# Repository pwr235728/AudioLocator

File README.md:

# AudioLocator
Urządzenie umożliwiające wykrycie kierunku nadchodzącego dźwięku o znanych parametrach (sinusoidalny, o znanej częstotliwość).

Urządzenie składa się z:
* dwóch mikrofonów
* dwóch wzmacniaczy mikrofonowych 
* mikrokontroler STM32.

Mikrokontroler na podstawie dźwięku przechwyconego mikrofonami, oblicza kierunek z którego nadchodzi dźwięk.

Docelowo urządzenie ma zostać wyposarzone w dodatkowe mikrofony i umożłiwiać wykrywanie pozycji 3D źródła dźwięku.

## Model pytki PCB ze wzmacniaczami mikrofonowymi:

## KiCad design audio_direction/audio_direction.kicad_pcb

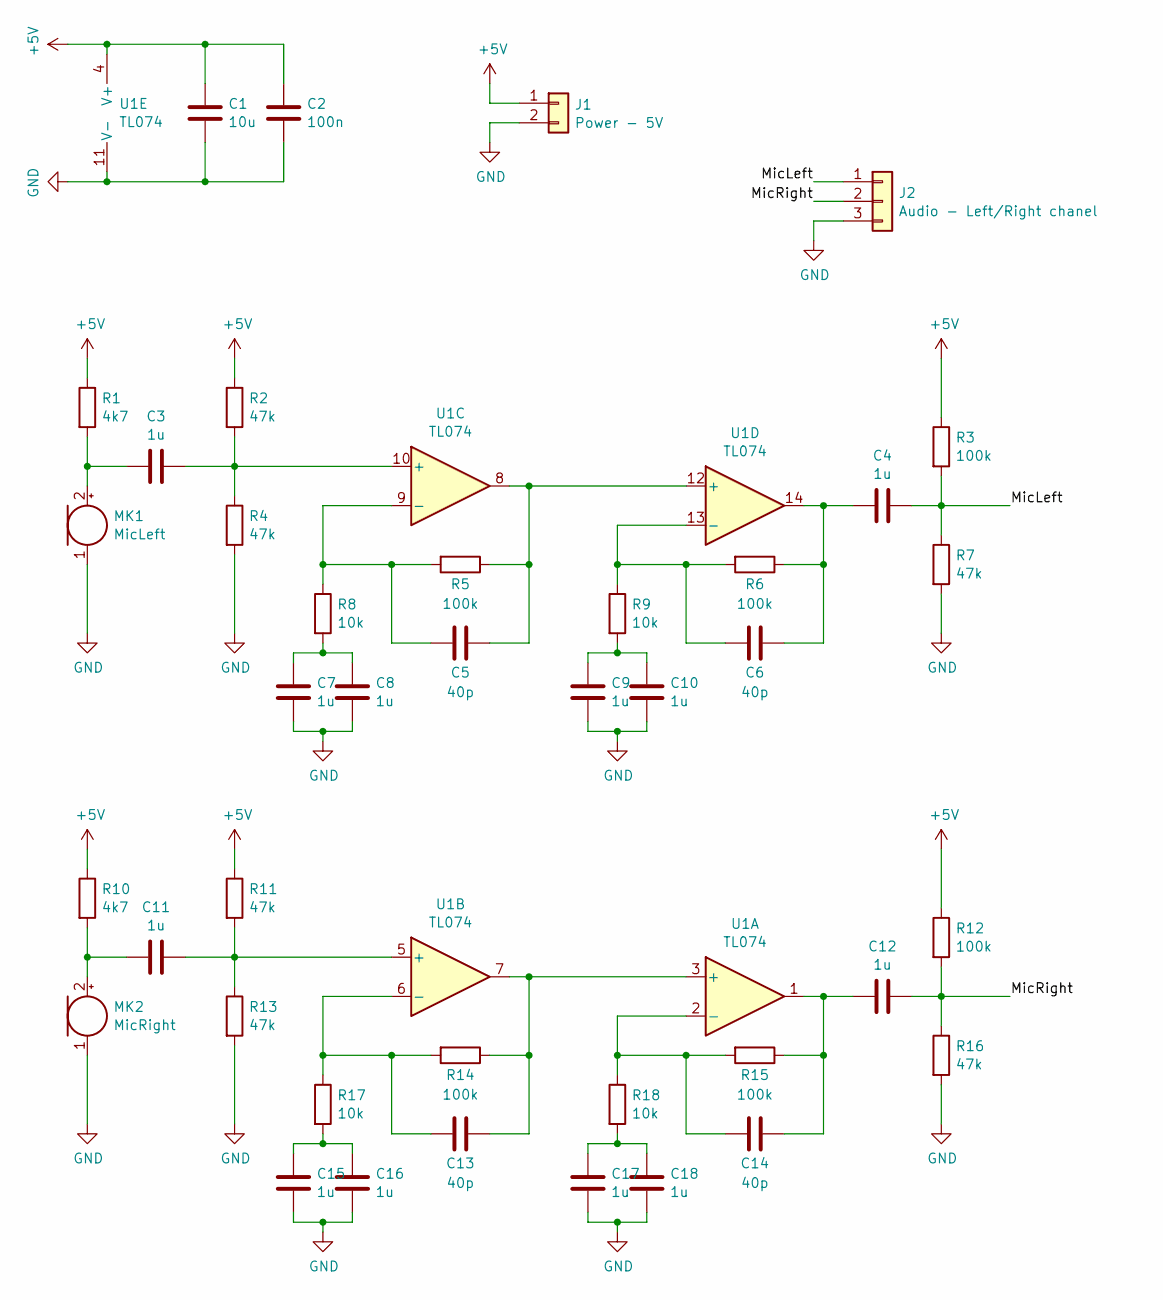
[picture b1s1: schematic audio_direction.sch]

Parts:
C1: 10u; C_0805_2012Metric_Pad1.15x1.40mm_HandSolder
C2: 100n; C_0805_2012Metric_Pad1.15x1.40mm_HandSolder
C3, C4, C7, C8, C9, C10, C11, C12, C15, C16, C17, C18: 1u; C_0805_2012Metric_Pad1.15x1.40mm_HandSolder
C5, C6, C13, C14: 40p; C_0805_2012Metric_Pad1.15x1.40mm_HandSolder
J1: Power - 5V; PinSocket_1x02_P2.54mm_Horizontal
J2: Audio - Left/Right chanel; PinSocket_1x03_P2.54mm_Horizontal
MK1: MicLeft; PinSocket_1x02_P2.54mm_Vertical
MK2: MicRight; PinSocket_1x02_P2.54mm_Vertical
R1, R10: 4k7; R_0805_2012Metric_Pad1.15x1.40mm_HandSolder
R2, R4, R7, R11, R13, R16: 47k; R_0805_2012Metric_Pad1.15x1.40mm_HandSolder
R3, R5, R6, R12, R14, R15: 100k; R_0805_2012Metric_Pad1.15x1.40mm_HandSolder
R8, R9, R17, R18: 10k; R_0805_2012Metric_Pad1.15x1.40mm_HandSolder
U1: TL074; DIP-14_W7.62mm_Socket_LongPads

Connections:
+5V: C1.2, C2.2, J1.1, R1.1, R2.1, R3.1, R10.1, R11.1, R12.1, U1.4 (V+)
/MicLeft: C4.1, J2.1, R3.2, R7.1
/MicRight: C12.1, J2.2, R12.2, R16.1
GND: C1.1, C2.1, C7.2, C8.2, C9.2, C10.2, C15.2, C16.2, C17.2, C18.2, J1.2, J2.3, MK1.1 (-), MK2.1 (-), R4.2, R7.2, R13.2, R16.2, U1.11 (V-)
unnamed: C3.1, R2.2, R4.1, U1.10 (+)
unnamed: C3.2, MK1.2 (+), R1.2
unnamed: C4.2, C6.1, R6.1, U1.14
unnamed: C5.1, R5.1, U1.8, U1.12 (+)
unnamed: C5.2, R5.2, R8.1, U1.9 (-)
unnamed: C6.2, R6.2, R9.1, U1.13 (-)
unnamed: C7.1, C8.1, R8.2
unnamed: C9.1, C10.1, R9.2
unnamed: C11.1, R11.2, R13.1, U1.5 (+)
unnamed: C11.2, MK2.2 (+), R10.2
unnamed: C12.2, C14.1, R15.1, U1.1
unnamed: C13.1, R14.1, U1.3 (+), U1.7
unnamed: C13.2, R14.2, R17.1, U1.6 (-)
unnamed: C14.2, R15.2, R18.1, U1.2 (-)
unnamed: C15.1, C16.1, R17.2
unnamed: C17.1, C18.1, R18.2

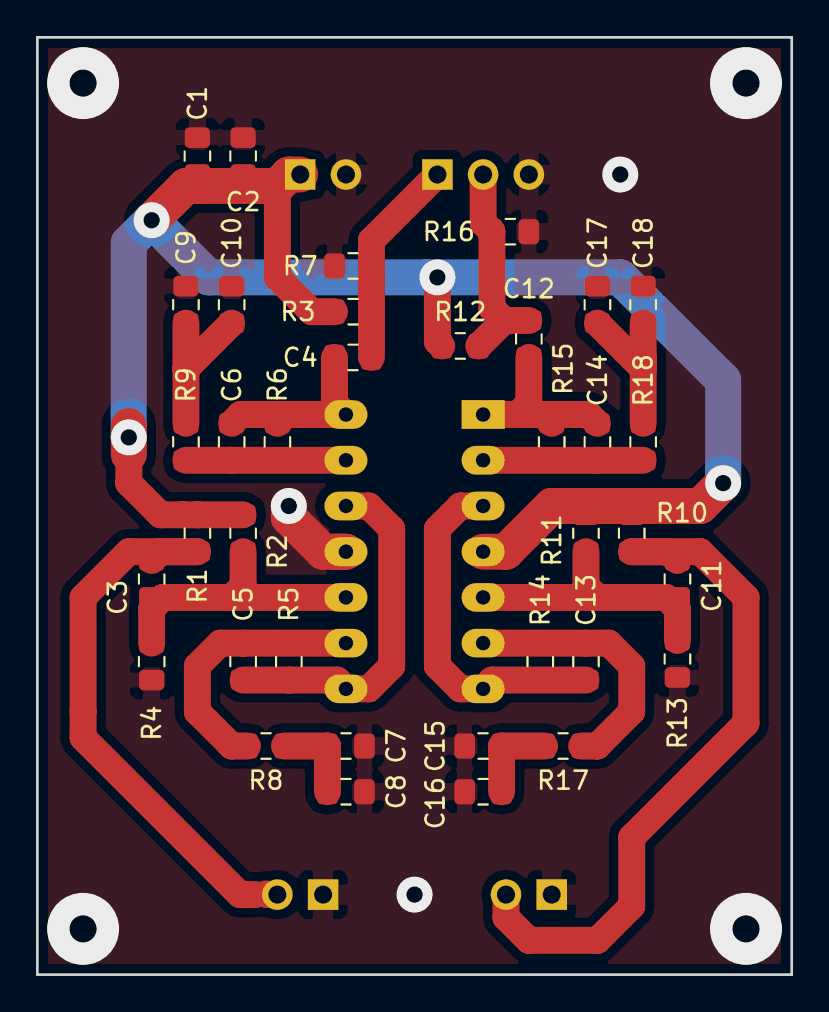
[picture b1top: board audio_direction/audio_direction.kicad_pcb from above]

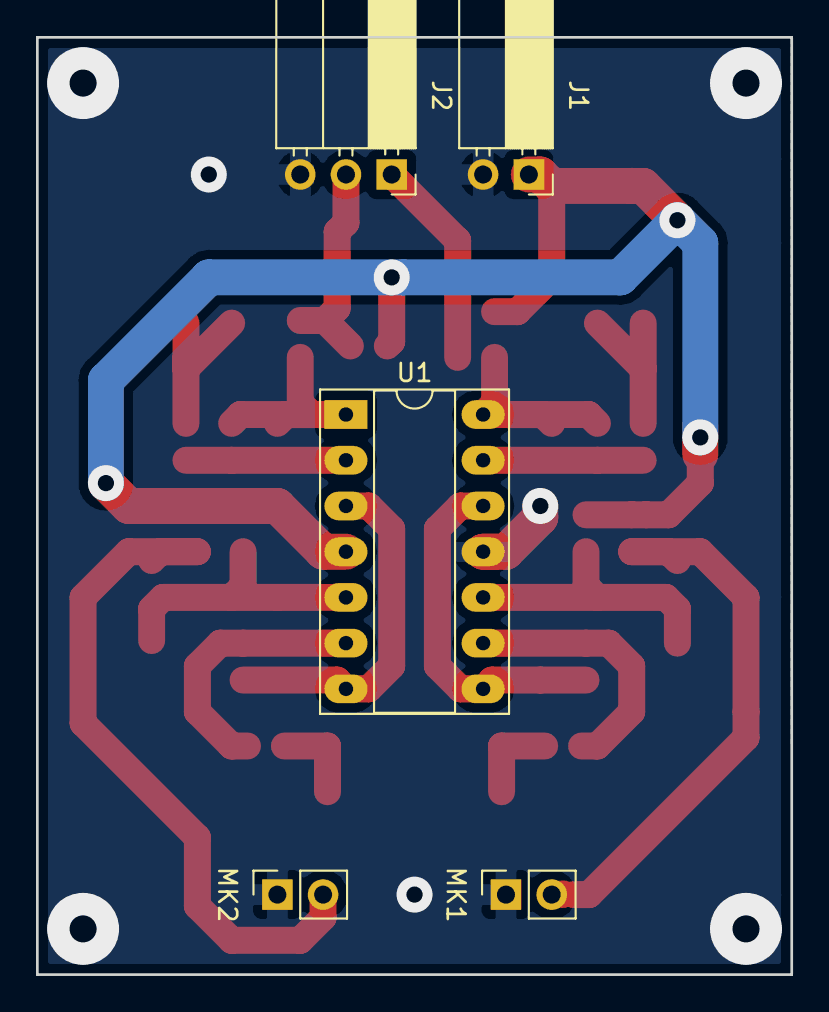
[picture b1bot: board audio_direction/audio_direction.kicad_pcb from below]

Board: 2 copper layers, 41.9 x 52.1 mm, 41 parts (5 on the bottom side), 20 nets.

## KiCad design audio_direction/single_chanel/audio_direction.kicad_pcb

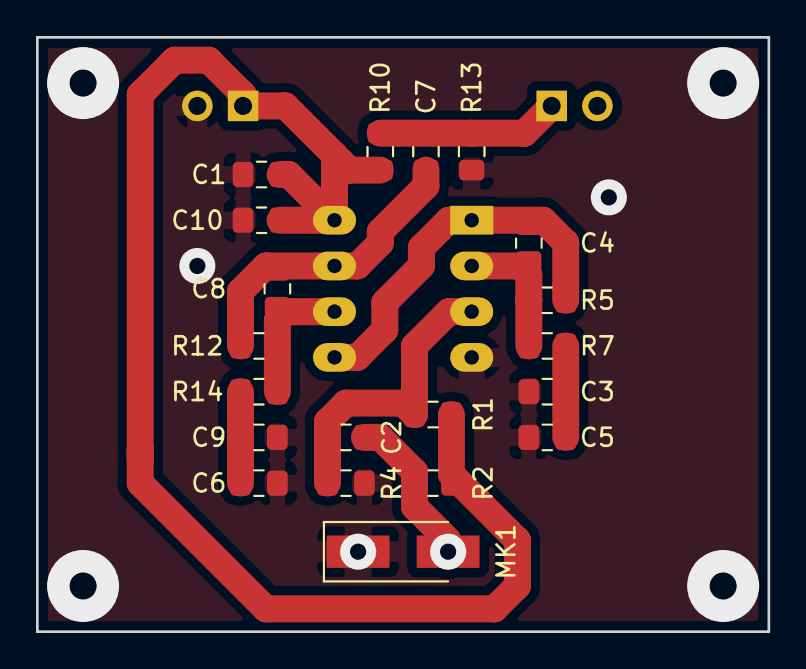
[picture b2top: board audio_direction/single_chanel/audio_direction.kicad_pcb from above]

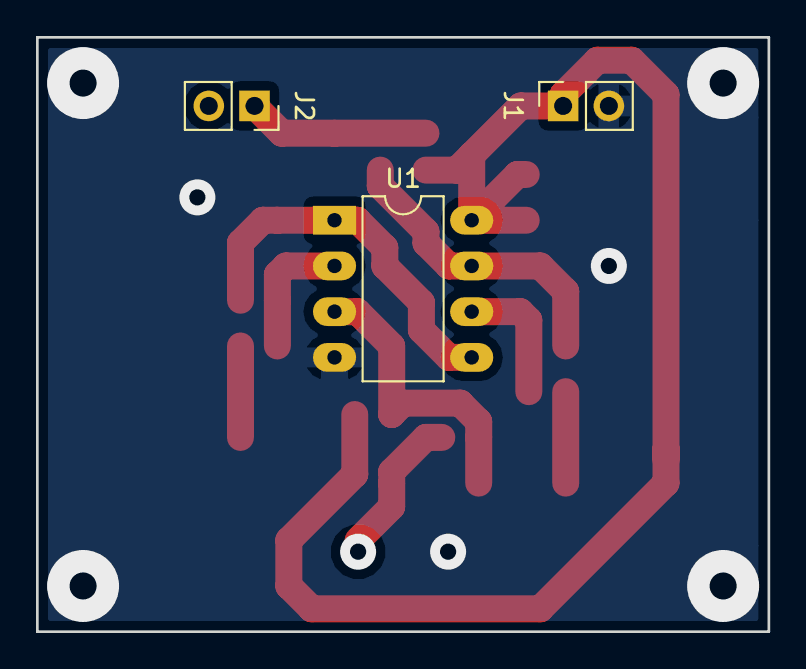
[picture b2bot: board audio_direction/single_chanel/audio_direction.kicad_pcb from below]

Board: 2 copper layers, 40.6 x 33.0 mm, 23 parts (3 on the bottom side), 11 nets.

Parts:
C1: 10u; C_0805_2012Metric_Pad1.15x1.40mm_HandSolder
C2, C3, C5, C6, C7, C9: 1u; C_0805_2012Metric_Pad1.15x1.40mm_HandSolder
C4, C8: 40p; C_0805_2012Metric_Pad1.15x1.40mm_HandSolder
C10: 100n; C_0805_2012Metric_Pad1.15x1.40mm_HandSolder
J1: Power - 5V; PinSocket_1x02_P2.54mm_Vertical
J2: Audio - Left/Right chanel; PinSocket_1x02_P2.54mm_Vertical
MK1: MicLeft; D_SMA_Handsoldering
R1, R4, R13: 47k; R_0805_2012Metric_Pad1.15x1.40mm_HandSolder
R2: 4k7; R_0805_2012Metric_Pad1.15x1.40mm_HandSolder
R5, R12: 90k; R_0805_2012Metric_Pad1.15x1.40mm_HandSolder
R7, R14: 10k; R_0805_2012Metric_Pad1.15x1.40mm_HandSolder
R10: 100k; R_0805_2012Metric_Pad1.15x1.40mm_HandSolder
U1: TL072; DIP-8_W7.62mm_LongPads

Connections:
+5V: C1.2, C10.2, J1.1, R1.1, R2.1, R10.1, U1.8
/MicLeft: C7.1, J2.1, R10.2, R13.1
GND: C1.1, C3.2, C5.2, C6.2, C9.2, C10.1, J1.2, MK1.1, R4.2, R13.2, U1.4
unnamed: C2.1, R1.2, R4.1, U1.3
unnamed: C2.2, MK1.2, R2.2
unnamed: C3.1, C5.1, R7.2
unnamed: C4.1, R5.1, U1.1, U1.5
unnamed: C4.2, R5.2, R7.1, U1.2
unnamed: C6.1, C9.1, R14.2
unnamed: C7.2, C8.1, R12.1, U1.7
unnamed: C8.2, R12.2, R14.1, U1.6

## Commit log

2019-10-14 Init
2019-10-14 image of pcb
2019-10-20 Implementacja Goertzel Filter do wykrycia częstotliwości i fazy sygnału
